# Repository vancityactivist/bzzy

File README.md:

# bzzy

A homebrew desk busy light: a small screen that shows GIFs, a ring of light around it, and a status (Free, Busy, Do not disturb, Away) set from your phone, your calendar, or the button on top of the device. It clips to a monitor and is powered over USB-C.

The companion app runs at **[bzzy.ca](https://bzzy.ca)**.

## What's in the repo

| Folder | What it is |
|---|---|
| [app/](app/README.md) | The companion app: Next.js on Vercel, Postgres on Neon (Drizzle), GIFs in Vercel Blob, sign-in with GitHub or a passkey |
| [firmware/](firmware/) | PlatformIO firmware for the Waveshare ESP32-S3 board |
| [hardware/](hardware/README.md) | The LED ring board (KiCad, rev C) and the printed case (OpenSCAD) |
| [docs/protocol.md](docs/protocol.md) | How the device and the app talk |
| [docs/ota.md](docs/ota.md) | Firmware updates over Wi-Fi |
| [docs/domains.md](docs/domains.md) | bzzy.ca, the redirect domains, DNS and email records |

## How it fits together

```
 ICS calendar feed ──▶ companion app (Next.js) ◀── phone / laptop
                         ▲          ▲
   firmware releases ────┘          │ device polls over HTTPS (outbound only)
   (GitHub Releases)                │
                               bzzy device ◀── button
```

The device never needs anything to connect *to* it, so it works on guest Wi-Fi that isolates devices. It saves the last state it received, so it keeps following your calendar and button presses if Wi-Fi or the app goes away. See [docs/protocol.md](docs/protocol.md).

## The app

- **Status:** set Free, Busy, Do not disturb or Away, or leave it on automatic. A live preview shows exactly what the light's screen and ring look like right now.
- **Show now:** put a GIF or a short message on the light straight away. It takes over the whole screen until you clear it.
- **Calendar:** add an ICS link (Settings → Calendars). Meetings make you Busy, out of office makes you Away, and a manual status still wins.
- **GIFs:** upload your own or paste a GIPHY or Tenor link, then pick one per status on the Devices page. Long GIFs are thinned out to fit the device.
- **Devices:** add a light, get its ID and token, choose its GIFs, and see its firmware version and updates.
- **Teams:** everyone gets a personal team. Devices, calendars and GIFs belong to a team.
- **Admin:** a sign-up and usage overview for admin users.

Signed out, the home page is a landing page about bzzy. The app has no cron jobs: calendars refresh when a device polls (every 20 seconds) or a page loads. See [app/README.md](app/README.md) to run it locally.

## Where it's at

Done:

1. Breadboard prototype firmware
2. Companion app with sign-in, teams, status, device API, GIFs, show now and the live preview
3. Calendar sync from an ICS link
4. Custom LED ring board (rev C) and a black case with a frosted light border, button cap and bzzy wordmark ([hardware/](hardware/README.md))
5. Signed firmware updates over Wi-Fi from GitHub Releases ([docs/ota.md](docs/ota.md))

Next:

- **Build the first one.** Measure the Waveshare board, order the ring board from JLCPCB, get the case printed, and test it all on real hardware.

### Later

- **Logo.** Design a proper bzzy logo in the style of the current wordmark: lowercase, black, tight letter spacing (Geist semibold, `tracking-tight`, as in the app's top bar). It should work as an app icon, a favicon, and on the case.
- **Pre-built lights.** Once the custom board is proven, offer assembled and tested bzzys for people who don't want to order and solder their own. The landing page already says they're coming.
- **Landing page photos.** The signed-out home page (`app/src/components/landing.tsx`) uses a concept picture and illustrations. Swap them for photos of a real bzzy once one is built.
- **v2 board.** One custom board with the ESP32-S3, the bare screen, USB-C and the LEDs (see [hardware/](hardware/README.md#v2-full-custom-board)).

## Hardware

The target board is the **touch** version. The non-touch board and a plain ESP32 still build, for testing.

The final design is the Waveshare board inside a custom LED ring board (16 LEDs, rev C) and a printed black case with a frosted border that glows in the status colour. See [hardware/](hardware/README.md) for the board, the case and the files to order. The parts below are for the breadboard prototype.

| Part | Part number to search | Notes |
|---|---|---|
| Main board (touch) | **Waveshare ESP32-S3-Touch-LCD-1.69**, SKU **27350** | ESP32-S3R8 (8 MB PSRAM), 16 MB flash, 1.69" 240×280 ST7789V2, CST816T touch, PCF85063 RTC, QMI8658 IMU, buzzer, USB-C |
| Main board (no touch, alternative) | Waveshare ESP32-S3-LCD-1.69, SKU 27932 | Same board without touch |
| LED ring (prototype) | WS2812B 12-LED ring, 50 mm (or Adafruit NeoPixel Ring 12, #1643) | |
| Push button (optional) | Any momentary switch | To try the top button: between GPIO18 and GND |
| Resistor | 330 Ω, 1/4 W | In series on the LED data line |
| Capacitor | 470 µF, 10 V or higher, electrolytic | Across LED 5 V / GND, near the LEDs |
| RTC backup cell (optional) | Rechargeable ML1220 with an SH1.0 2-pin lead | Keeps the clock through power cuts. Without it, the clock comes back from NTP once Wi-Fi does |

**Wiring (touch board):** LED data to **GPIO17**, LED 5 V to the board's 5 V pin, GND to GND. The free pins on this board are 2, 3, 17 and 18. Avoid 3, which is a strapping pin. LED current is capped at 400 mA in firmware. The top button goes from **GPIO18** to GND (the firmware turns on the pull-up).

On the non-touch board the LED data pin is GPIO16. On a generic ESP32 it's GPIO13.

## Firmware

Built with [PlatformIO](https://platformio.org/).

```sh
cd firmware
pio run -e waveshare_s3_touch_lcd169 -t upload   # the real board (touch)
pio run -e waveshare_s3_lcd169 -t upload         # non-touch version
pio run -e esp32_generic -t upload               # a plain ESP32: LEDs, Wi-Fi and sync only
pio test -e native                               # status logic unit tests, no hardware needed
pio device monitor
```

**First boot / changing Wi-Fi:** with nothing saved, or if you hold the BOOT button (or the top button on the final hardware) for 3 seconds while plugging in, the device opens a Wi-Fi network called `bzzy-setup`. Join it from your phone, pick your Wi-Fi, and fill in the companion app URL, device ID and token.

**Controls:** tap the screen (or press BOOT, or the top button on the final hardware) to step Free → Busy → Do not disturb → back to automatic. Long-press the screen or the top button for one second to go straight back to automatic (calendar or default).

**Updates:** after the first USB flash, lights update themselves over Wi-Fi from GitHub Releases: push a tag like `fw-v0.3.0`. Updates are signed, wait until you're free or away, and roll back if the new firmware can't reach the app. See [docs/ota.md](docs/ota.md) for the one-time setup (a signing key).

**GIFs:** pick one per status on the app's Devices page (built-in or your own uploads from the GIFs page). The device downloads a GIF when it changes and keeps it in flash, so it still plays offline. Choosing "No GIF" shows a coloured card with large text.

### When things go wrong

| Situation | What it shows |
|---|---|
| Wi-Fi or app down | Last-known status and calendar, small hollow ring in the corner |
| No good data for 24 h, or clock never set | Slow grey breathing light, "?" and a note on screen |
| Power cut with no Wi-Fi | Clock comes back from the board's RTC, cached calendar keeps working |

### Not done yet

- HTTPS certificate checking is off (`setInsecure`) for the app connection. Firmware updates don't depend on it: they're checked against a signature.
- Untested on real hardware: pin numbers come from Waveshare's V2 schematic, and the board dimensions the case and ring use are estimates until someone measures one.

## License

bzzy is free to build and use, but not to sell. The software (app and firmware) is under [PolyForm Noncommercial 1.0.0](LICENSES/PolyForm-Noncommercial-1.0.0.md) and the hardware (ring board and case) under [CC BY-NC-SA 4.0](LICENSES/CC-BY-NC-SA-4.0.txt). Using a light you built at your own job is fine. See [LICENSE.md](LICENSE.md) for details, and ask if you'd like to buy one.

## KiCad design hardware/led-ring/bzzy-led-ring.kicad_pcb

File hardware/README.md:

# bzzy hardware

The final device is a frame of light around the screen. It has four parts:

1. The **Waveshare ESP32-S3-Touch-LCD-1.69**, the brains and the screen. It's unchanged from the prototype.
2. A custom **LED ring board** with 16 small RGB LEDs. It sits around the Waveshare board.
3. A printed **frosted white border**, about 1 cm wide, round the screen. The LEDs light it in the status colour.
4. A printed **black case** round all of it, with a button on top, the bzzy wordmark, and a monitor clip.

Nothing changes in the firmware. The ring board uses the same data pin (GPIO17) and LED count (16) that `firmware/src/config.h` already has.

This is **rev C, a concept**. Rev C opens the bottom of the ring so a USB-C plug can reach the Waveshare socket (rev B added the button on top). The board has been through KiCad's design-rule check, but nobody has built one yet. Measure the Waveshare board before you order anything (see [Before you order](#before-you-order)).

| Front | Busy (lit red) | Top: button and wordmark |
|---|---|---|
|  |  |  |
| **Back, with the clip** | **Exploded** | |
|  |  | |

## Plan

- **Now (rev C):** an LED ring board around the Waveshare board, with a button on top, plus a printed case. It's cheap and quick to get made.
- **v2 (later):** one custom board with the ESP32-S3, the bare screen, USB-C and the LEDs. See [v2: full custom board](#v2-full-custom-board).

## How it fits together

```mermaid
flowchart LR
  USB[USB-C 5 V] --> WS[Waveshare ESP32-S3<br/>screen, touch, RTC]
  WS -- "5V, GND, GPIO17<br/>(3 wires)" --> J1[J1 wire pads]
  J2[J2 wire pad] -- "GPIO18<br/>(1 wire)" --> WS
  subgraph ring [LED ring board]
    J1 --> U1[74AHCT1G125<br/>3.3 V to 5 V data]
    U1 --> R2[33 Ω] --> D1[D1] --> D2[D2 ... D15] --> D16[D16] --> TP1[TP1: to add more LEDs]
    SW1[SW1 top button<br/>to GND] --> J2
  end
```

## LED ring board

Files are in [led-ring/](led-ring/). Open `bzzy-led-ring.kicad_pro` in KiCad 7 or later.

| | |
|---|---|
| Size | 52 × 61 mm, 2 layers, 1.6 mm. The 34.2 × 42.7 mm cutout fits the Waveshare board. A 14 mm notch at the bottom middle opens the cutout to the edge, so the USB-C plug can pass through the ring. No copper within 2.7 mm of the M2 holes, so screw heads sit on bare board |
| LEDs | 16 × WS2812B-2020 (2 × 2 mm), every 10 to 12 mm, chained clockwise from just left of the notch |
| Data | GPIO17 (3.3 V), then a 74AHCT1G125 buffer to 5 V logic, then 33 Ω to the first LED. A 100 kΩ pull-down keeps the LEDs dark while the ESP32 boots |
| Power | 5 V from the Waveshare board's 5V pad. A 0.8 mm power ring on the back, a 100 nF cap per LED, and 2 × 10 µF bulk caps. Firmware caps the LEDs at 400 mA |
| Connection | J1 is three plated holes on the left side (5V, GND, IO17 from top to bottom, labelled on the back). J2 is one plated hole at the top, right of the button (IO18). Both are clear of the USB-C plug. Solder four short wires to the Waveshare board's 5V, GND, GPIO17 and GPIO18 pads |
| Top button | SW1, an Alps SKRT side-push switch on the top edge, with its plunger pointing up. You press it through a black button cap in the case's top wall. It shorts GPIO18 to GND, and the firmware turns on the internal pull-up |
| Mounting | 4 × M2 holes in the corners. The screws go through the case's back plate and the ring board into the light ring |
| Assembly | Every part is on the front, so JLCPCB assembles one side only. You hand-solder the J1 and J2 wires |

| Front (LEDs) | Back (+5V ring, GND pour) |
|---|---|
|  |  |

### How it's made

[`led-ring/gen_led_ring.py`](led-ring/gen_led_ring.py) is the source of truth. It writes these files:

- the KiCad schematic, with connectivity checked against the script's netlist
- the PCB, with parts placed, traces routed and ground poured
- `fab/bom-jlcpcb.csv` and `fab/cpl-jlcpcb.csv`, for JLCPCB assembly
- `fab/drc-report.txt`. Rev C: **0 violations, 0 unconnected pads**. The switch's own land pattern puts its pads closer to its peg holes than the board rule allows, so `bzzy-led-ring.kicad_dru` allows that within SW1 only
- `case/board_dims.scad`, so the case always matches the board

The ring is regular, so the script routes it by rule instead of with an autorouter. Each LED's 5 V pad drops through a via onto the power ring. Its ground pad joins the ground pour. Its data out runs straight to the next LED, and the corners go round the screen side of the mounting holes.

To change something, edit the script and run `./render.sh` (needs KiCad 7+ and OpenSCAD). Once the design settles, you can stop using the script and edit the board directly in KiCad.

### Bill of materials (per board)

| Ref | Qty | Part | Package | Notes |
|---|---|---|---|---|
| D1 to D16 | 16 | WS2812B-2020 | 2020 | Addressable RGB LED |
| U1 | 1 | 74AHCT1G125 | SOT-23-5 | Level shifter. A 74HCT1G125 works too |
| C1, C4 to C19 | 17 | 100 nF, X7R, 16 V | 0402 | |
| C2, C3 | 2 | 10 µF, X5R, 10 V+ | 0805 | |
| R1 | 1 | 100 kΩ | 0402 | |
| R2 | 1 | 33 Ω | 0402 | |
| SW1 | 1 | Alps SKRTLAE010 | SMD side-push | Top button |
| J1 | – | 3 plated holes, 2.54 mm | – | Wires, hand-soldered |
| J2 | – | 1 plated hole, 1.5 mm pad | – | Wire to GPIO18, hand-soldered |
| Screws | 4 | M2 × 8 self-tapping (or M2 × 8 with heat-set inserts in the light ring) | | |

`fab/bom-jlcpcb.csv` has an LCSC part number for every line (set in `gen_led_ring.py`). Check each match in JLCPCB's BOM step, and swap in a Basic part where one fits, since each Extended part adds a small fee. The WS2812B-2020, the 74AHCT1G125 and the SKRTLAE010 are probably Extended.

`fab/cpl-jlcpcb.csv` uses the same coordinates as the Gerbers, and its rotations already include JLCPCB's usual offsets (+180° for SOT-23-5, +90° for the WS2812B-2020). JLCPCB's own footprint decides the real orientation, so still check the preview.

**Rough cost:** about US$30 to $50 for 5 assembled boards before shipping and duty. That's an estimate, not a quote.

## Case

[`case/bzzy_case.scad`](case/bzzy_case.scad) is parametric OpenSCAD. The case is black, with the screen in the middle of a frosted white border about 1 cm wide (9.2 mm at the sides, 9.5 mm top and bottom). The LEDs sit under the border. Overall it's about 58 × 67 × 15 mm, plus the clip.

Looking at the front, from the middle out: the screen, a thin black trim over the Waveshare board's own glass edge, the frosted border, then a 1.4 mm black rim. The border starts at the Waveshare board's edge, not at the lit screen, because no LED can sit under the board. The ring board didn't need to change for this.

Export a part with:

```sh
openscad -D 'PART="light"' -o light.stl case/bzzy_case.scad   # or frame, back, trim, button, clip
```

`./render.sh` exports all six to `case/stl/`, each already turned the way it prints best. They aren't committed until the measurements are confirmed.

| Part | Colour and material | Notes |
|---|---|---|
| light | **Frosted white.** Translucent white PETG, or clear or white resin (SLA) with a matte finish | The glowing border. 1.6 mm thick at the front, about 2.4 mm in front of the LEDs. Its outer lip sits over the frame's rim, and four bosses take the screws. Print it face down |
| frame | **Black.** PLA, PETG, or MJF nylon (PA12, dyed black) | Front rim and the four side walls, with the USB-C opening and BOOT pinhole on the bottom, and the button hole and wordmark on top. Print it face down |
| back | **Black** | Back plate. Four posts press the ring board forward and the screws go through them. Dovetail rail for the clip |
| trim | **Black** | Sleeve round the Waveshare board, with the thin trim round the screen. Keeps LED light off the display. The light ring holds it down |
| button | **Black** | Cap for the top button. Sits in a pocket in the frame's top wall, held in by its flange. Print it flange down |
| clip | **Black.** PETG or nylon (needs some flex) | Slides up the rail. Two legs rest on the monitor's top edge, with a lip at the front and a drop at the back. Set `MONITOR_T` to your monitor's thickness |

**For a print service** (JLC3DP, Craftcloud, a local shop): order `light.stl` in translucent or white resin, and the other five in black. MJF nylon in black is tough and has no visible layers, which suits the frame and clip. Resin is fine for the light ring, but ask for the "translucent" or "semi-transparent" option with a matte or sanded finish, so the LEDs don't show as dots. None of the parts need supports in the orientation they're exported in, except the back plate, which stands on its rail. Ask the service to orient it, or use MJF or resin, where it doesn't matter.

### How it goes together

1. Put the button cap into its pocket in the frame's top wall, from the inside.
2. Hold the frame face up and drop the light ring in from the front, so its lip sits on the frame's rim. Turn the two over together, face down on the table.
3. Put the trim in from the back, face down, through the light ring's middle.
4. Put the ring board, LEDs down, onto the light ring's bosses, then the Waveshare board into the trim. The button cap now rests just off the switch.
5. Put a square of 3 mm foam tape on the back of the Waveshare board, then put the back plate on and do up the four M2 screws. They pull the light ring back, and its lip clamps the frame's rim against the back plate. No glue.
6. Slide the clip up the rail.

### The top button

The switch only travels 0.2 mm, and its plunger tip sits on the board's routed edge, which is only accurate to about ± 0.2 mm. So the cap rests 0.1 mm off the plunger and can float 0.5 mm outwards. A board that comes back slightly large pushes the cap out a little, instead of holding the switch down. If the switch were held down, the device would boot into setup every time. `TOP_BTN_Z` is the plunger's height above the board (0.8 mm for the Alps SKRT). Check it against the switch once you have one.

### The wordmark

"bzzy" is debossed 0.6 mm into the top face, right of the button, in Geist SemiBold, the font the app uses, with tight tracking. The font is in `case/fonts/` (SIL Open Font License). Set `LOGO` to move it:

| `LOGO` | Where |
|---|---|
| `"top"` (default) | Top face, right of the button. People standing at your desk see it |
| `"chin"` | Front, in a 9 mm black chin below the border. The device gets taller and the screen sits above centre |
| `"back"` | Back plate, above the clip rail. Hidden when the device is on the monitor |
| `"none"` | No wordmark |

## Before you order

Waveshare only publishes the board's outline as a drawing, which I couldn't read from here, so a few numbers are **estimates**. With calipers, measure:

1. **The Waveshare board's width, height and total thickness** (`WS_W`, `WS_H`, `WS_T` in `gen_led_ring.py`). The cutout and case follow from these. I used 33.0 × 41.5 × 9.5 mm.
2. **Where the screen sits**: the visible area's size, and whether it's centred on the board (`SCREEN_*`, `SCREEN_DY` in the case).
3. **The glass height**: when the Waveshare board sits in the ring's cutout, how far its glass stands proud of the ring board's front face (`GLASS_Z`).
4. **USB-C and BOOT button positions** (`USB_*`, `BOOT_*`). I assumed the USB-C socket is on the bottom edge, in the middle. The rev C ring board has a 14 mm notch at the bottom middle for the plug. Check that your cable's plug moulding (12 × 6.5 mm assumed) fits through it.
5. **Your monitor's top edge thickness** (`MONITOR_T`).

Then print the frame, light ring and back once in cheap PLA to check the fit before ordering boards.

## Ordering from JLCPCB

1. Run `./render.sh`, which writes `led-ring/fab/gerbers.zip`. Or, in KiCad, export Gerbers and drill files (File, Fabrication Outputs) with JLCPCB's KiCad settings, and zip the folder.
2. Upload the zip at jlcpcb.com. Defaults are fine: 2 layers, 1.6 mm, HASL lead-free or ENIG, any colour. Black or white looks best behind a translucent frame.
3. Turn on **PCB Assembly**, top side, and upload `fab/bom-jlcpcb.csv` and `fab/cpl-jlcpcb.csv`.
4. In the parts-matching step, confirm the LCSC part on each line. In the placement preview, **check every LED, U1 and SW1**: the pin 1 dot should match the KiCad drawing. U1 matters most: placed backwards, it gets 5 V on its GND pin. Fix any rotation in the preview if needed.

## v2: full custom board

These are notes for later, once the ring board has proven the case and the light.

- **MCU:** an ESP32-S3-WROOM-1-N16R8 module. It has the same 16 MB flash and 8 MB PSRAM as the Waveshare board, plus a certified antenna. Keep the module's antenna end at the top edge, with no copper or LEDs under it.
- **Screen:** the bare 1.69" 240 × 280 ST7789V2 panel with CST816T touch on an FPC connector. Waveshare sells the panel separately as the "1.69inch Touch LCD Module". Find the panel's FPC pinout before laying out.
- **Pins:** keep the Waveshare mapping (LCD 4 to 8 and 15, I2C 10 and 11, touch 13 and 14, LEDs 17, top button 18, BOOT 0). The firmware then only needs a new PlatformIO env, or none at all.
- **Power:** USB-C into the S3's native USB (GPIO19 and 20), with 5.1 kΩ CC resistors, ESD protection and a fuse. A 3.3 V LDO rated 1 A for the S3's Wi-Fi peaks, and the LEDs straight off 5 V.
- **Keep:** PCF85063 RTC with a coin cell or supercap, and the BOOT and RESET buttons.
- **Drop:** the IMU, buzzer and Li-ion charger, unless there's a reason to keep them.
- **Result:** one board, roughly the ring board's size. That makes the case thinner and the build simpler, with no wires between boards.

## Open questions

- Are 16 LEDs enough? Firmware handles more, and TP1 lets you chain extras.

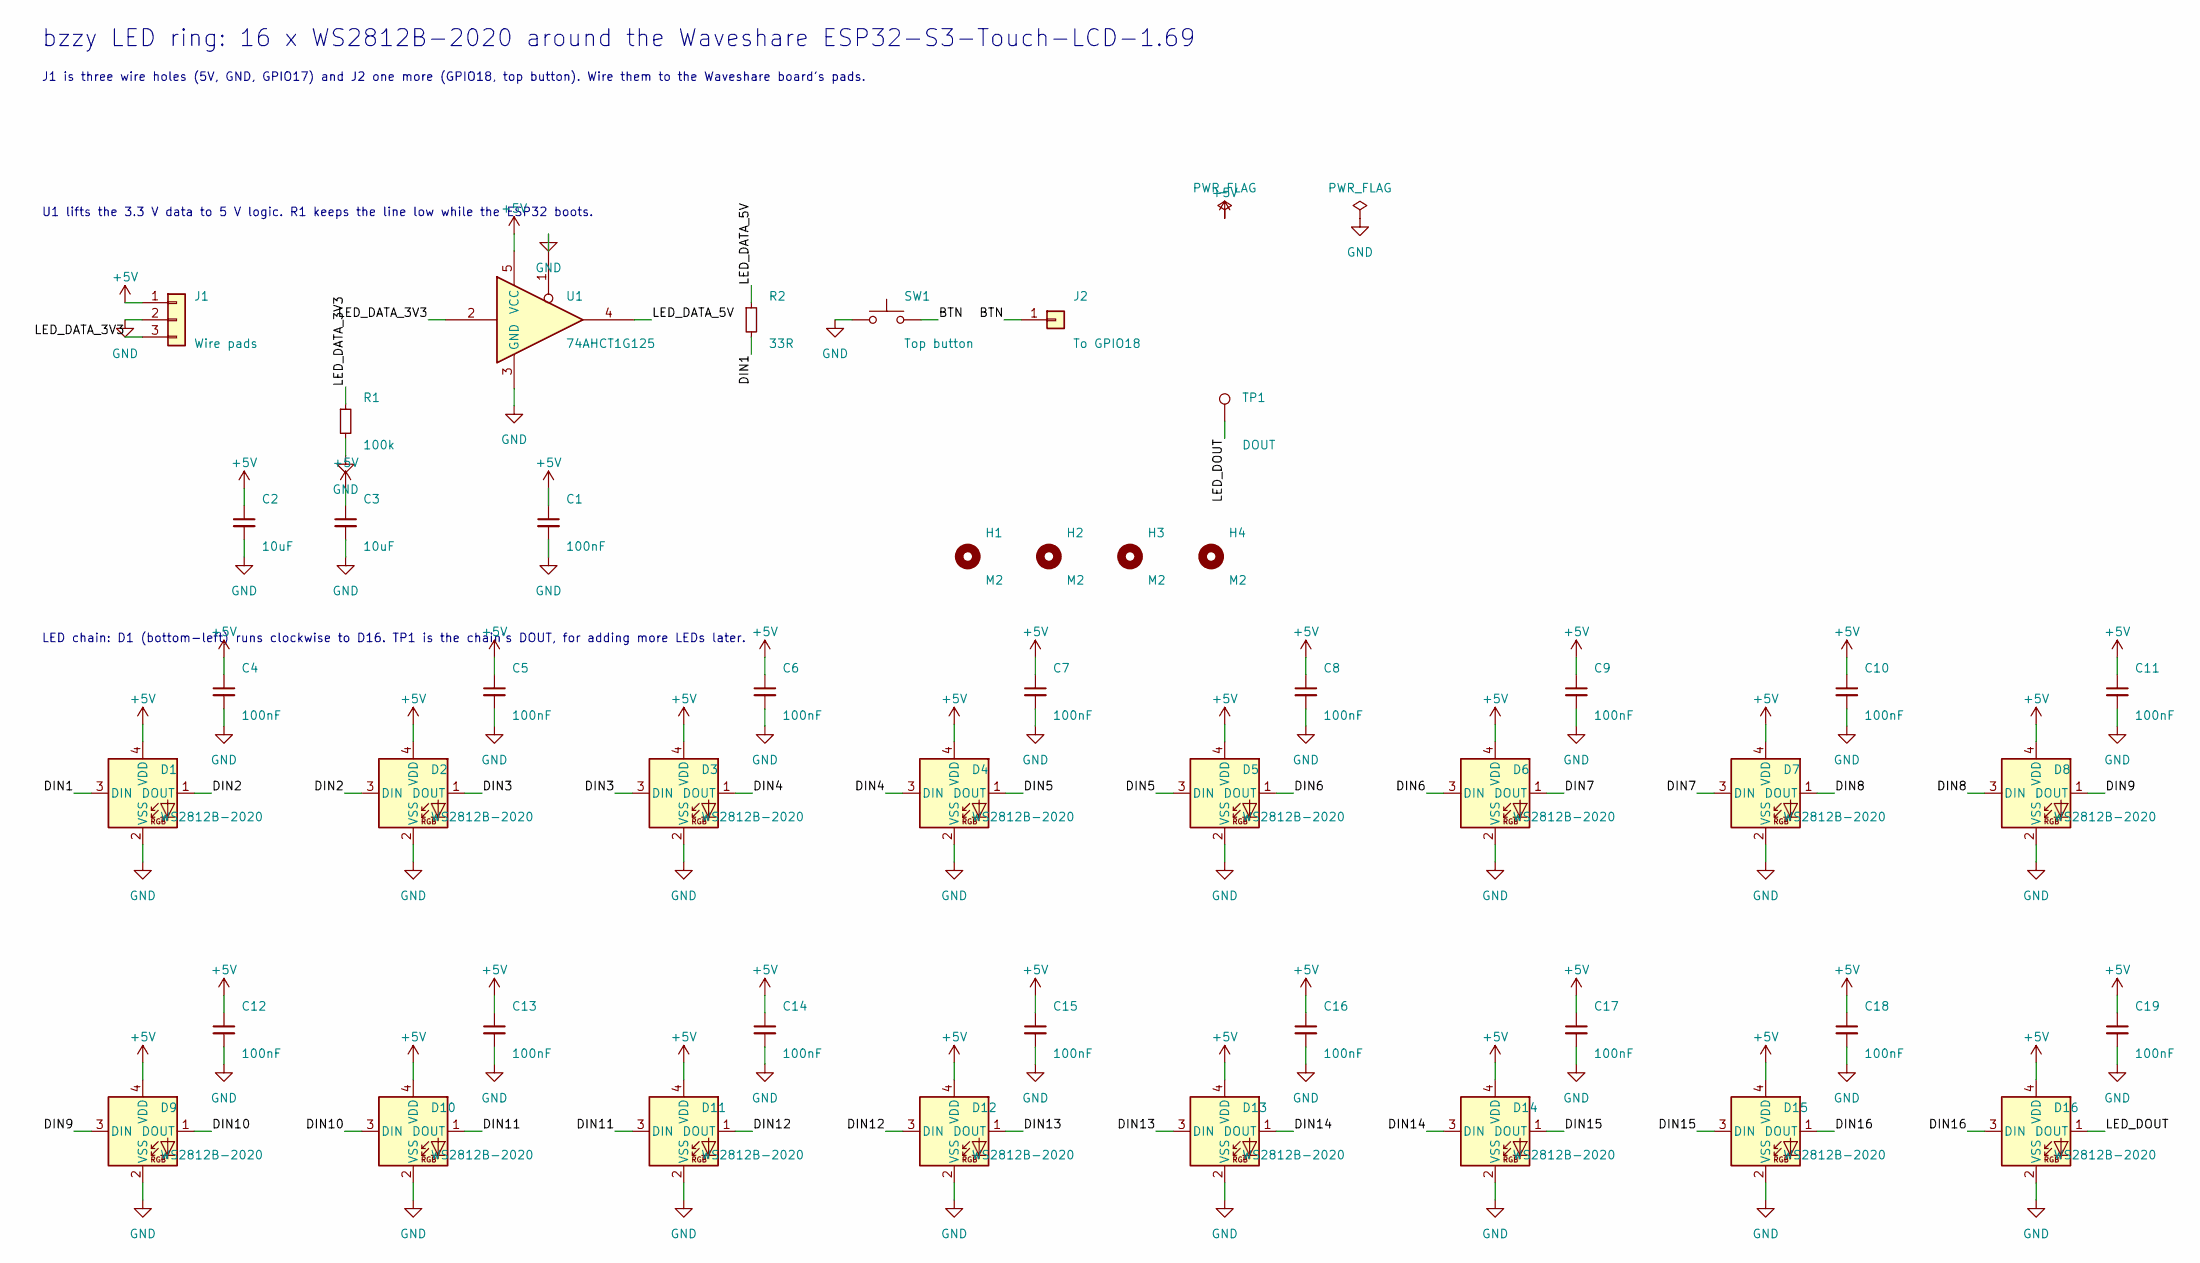
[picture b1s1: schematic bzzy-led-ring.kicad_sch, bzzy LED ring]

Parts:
C1, C4, C5, C6, C7, C8, C9, C10, C11, C12, C13, C14, C15, C16, C17, C18, C19: 100nF; C_0402_1005Metric; MPN CL05B104KO5NNNC
C2, C3: 10uF; C_0805_2012Metric; MPN CL21A106KAYNNNE
D1, D2, D3, D4, D5, D6, D7, D8, D9, D10, D11, D12, D13, D14, D15, D16: WS2812B-2020; LED_WS2812B-2020_PLCC4_2.0x2.0mm; MPN WS2812B-2020
H1, H2, H3, H4: M2; MountingHole_2.2mm_M2
J1: Wire pads; PinHeader_1x03_P2.54mm_Vertical
J2: To GPIO18; TestPoint_THTPad_1.5x1.5mm_Drill0.7mm
R1: 100k; R_0402_1005Metric; MPN 0402WGF1003TCE
R2: 33R; R_0402_1005Metric; MPN 0402WGF330JTCE
SW1: Top button; SW_Push_1P1T-MP_NO_Horizontal_Alps_SKRTLAE010; MPN SKRTLAE010
TP1: DOUT; TestPoint_Pad_D1.0mm
U1: 74AHCT1G125; SOT-23-5; MPN 74AHCT1G125GV,125

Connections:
+5V: C1.1, C2.1, C3.1, C4.1, C5.1, C6.1, C7.1, C8.1, C9.1, C10.1, C11.1, C12.1, C13.1, C14.1, C15.1, C16.1, C17.1, C18.1, C19.1, D1.4 (VDD), D2.4 (VDD), D3.4 (VDD), D4.4 (VDD), D5.4 (VDD), D6.4 (VDD), D7.4 (VDD), D8.4 (VDD), D9.4 (VDD), D10.4 (VDD), D11.4 (VDD), D12.4 (VDD), D13.4 (VDD), D14.4 (VDD), D15.4 (VDD), D16.4 (VDD), J1.1, U1.5 (VCC)
BTN: J2.1, SW1.2
DIN1: D1.3 (DIN), R2.2
DIN2: D1.1 (DOUT), D2.3 (DIN)
DIN3: D2.1 (DOUT), D3.3 (DIN)
DIN4: D3.1 (DOUT), D4.3 (DIN)
DIN5: D4.1 (DOUT), D5.3 (DIN)
DIN6: D5.1 (DOUT), D6.3 (DIN)
DIN7: D6.1 (DOUT), D7.3 (DIN)
DIN8: D7.1 (DOUT), D8.3 (DIN)
DIN9: D8.1 (DOUT), D9.3 (DIN)
DIN10: D9.1 (DOUT), D10.3 (DIN)
DIN11: D10.1 (DOUT), D11.3 (DIN)
DIN12: D11.1 (DOUT), D12.3 (DIN)
DIN13: D12.1 (DOUT), D13.3 (DIN)
DIN14: D13.1 (DOUT), D14.3 (DIN)
DIN15: D14.1 (DOUT), D15.3 (DIN)
DIN16: D15.1 (DOUT), D16.3 (DIN)
GND: C1.2, C2.2, C3.2, C4.2, C5.2, C6.2, C7.2, C8.2, C9.2, C10.2, C11.2, C12.2, C13.2, C14.2, C15.2, C16.2, C17.2, C18.2, C19.2, D1.2 (VSS), D2.2 (VSS), D3.2 (VSS), D4.2 (VSS), D5.2 (VSS), D6.2 (VSS), D7.2 (VSS), D8.2 (VSS), D9.2 (VSS), D10.2 (VSS), D11.2 (VSS), D12.2 (VSS), D13.2 (VSS), D14.2 (VSS), D15.2 (VSS), D16.2 (VSS), J1.2, R1.2, SW1.1, U1.1, U1.3 (GND)
LED_DATA_3V3: J1.3, R1.1, U1.2
LED_DATA_5V: R2.1, U1.4
LED_DOUT: D16.1 (DOUT), TP1.1

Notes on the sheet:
bzzy LED ring: 16 x WS2812B-2020 around the Waveshare ESP32-S3-Touch-LCD-1.69
J1 is three wire holes (5V, GND, GPIO17) and J2 one more (GPIO18, top button). Wire them to the Waveshare board's pads.
U1 lifts the 3.3 V data to 5 V logic. R1 keeps the line low while the ESP32 boots.
LED chain: D1 (bottom-left) runs clockwise to D16. TP1 is the chain's DOUT, for adding more LEDs later.

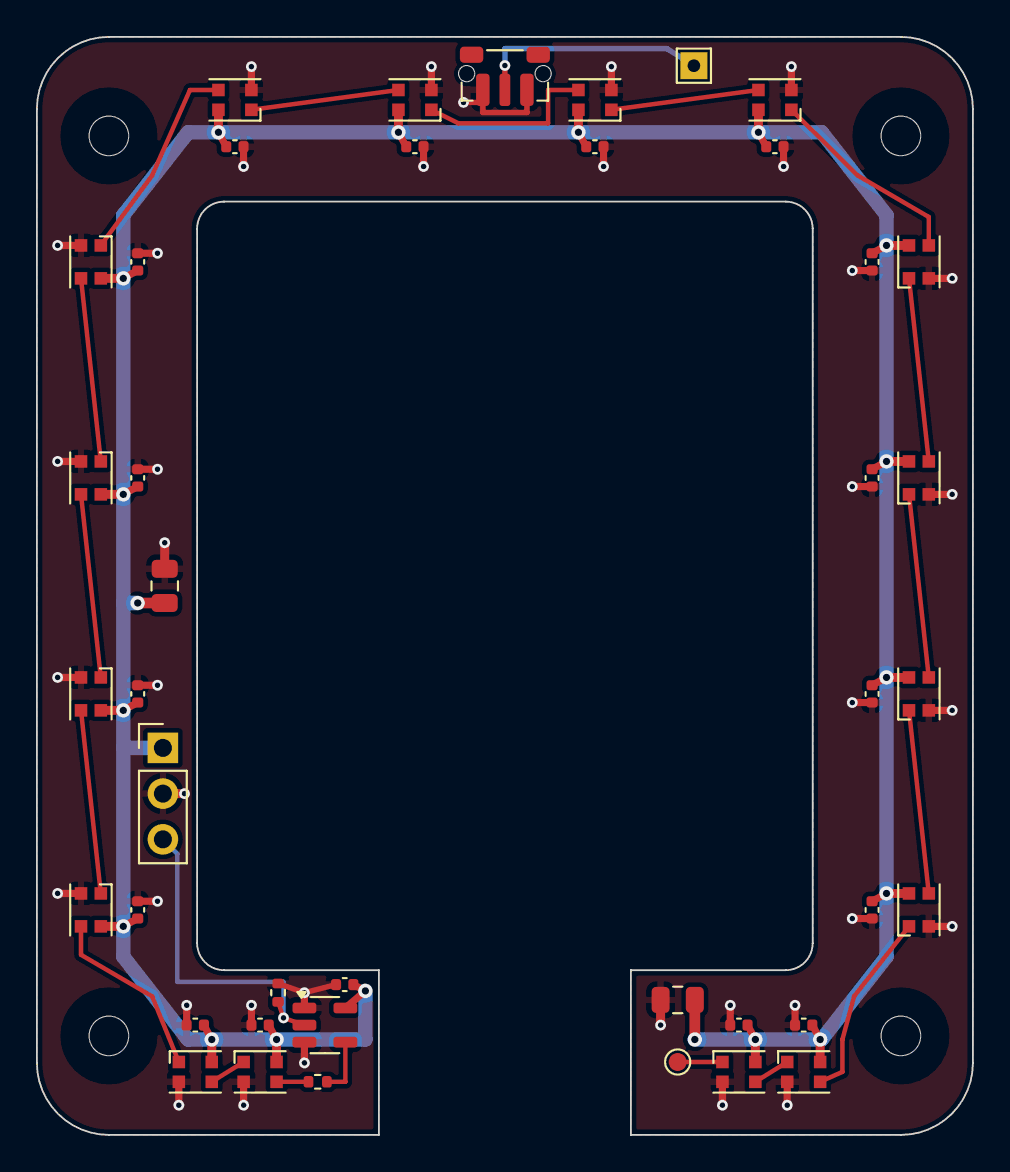
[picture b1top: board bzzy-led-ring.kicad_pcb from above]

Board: 2 copper layers, 52.0 x 61.0 mm, 46 parts (0 on the bottom side), 22 nets.

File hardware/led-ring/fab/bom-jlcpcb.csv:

Comment,Designator,Footprint,MPN,Qty,LCSC Part #
100k,R1,R_0402_1005Metric,0402WGF1003TCE,1,C25741
74AHCT1G125,U1,SOT-23-5,"74AHCT1G125GV,125",1,C12494
100nF,"C1,C4,C5,C6,C7,C8,C9,C10,C11,C12,C13,C14,C15,C16,C17,C18,C19",C_0402_1005Metric,CL05B104KO5NNNC,17,C1525
33R,R2,R_0402_1005Metric,0402WGF330JTCE,1,C25105
10uF,"C2,C3",C_0805_2012Metric,CL21A106KAYNNNE,2,C15850
WS2812B-2020,"D1,D2,D3,D4,D5,D6,D7,D8,D9,D10,D11,D12,D13,D14,D15,D16",LED_WS2812B-2020_PLCC4_2.0x2.0mm,WS2812B-2020,16,C965555
Top button,SW1,SW_Push_1P1T-MP_NO_Horizontal_Alps_SKRTLAE010,SKRTLAE010,1,C110293
